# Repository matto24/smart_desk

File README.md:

# Desk Controller

Open-hardware controller for a motorized (sit/stand) desk. A
[Seeed XIAO ESP32-C6](https://wiki.seeedstudio.com/xiao_esp32c6_getting_started/)
measures the desk height with a VL53L1X time-of-flight lidar and drives the
desk's up/down motor lines until it reaches a requested height, exposed over a
small WiFi web server that [Home Assistant](#home-assistant) can control.

> `skrivebord` is Danish for *desk*.

<p align="center">
  
  <br>
  <em>The press-fit 3D-printed enclosure — sensor opening on top, ventilation slots on the front.</em>
</p>

## How it works

- The ESP32-C6 hosts three HTTP endpoints. Each replies only once the action
  is finished, with the measured height as JSON:

  | Request | Action | Reply |
  |---------|--------|-------|
  | `GET /target?cm=90` | Move to 90 cm | `{"height":90.1}` |
  | `GET /nudge?cm=1` (or `-1`) | Move 1 cm up (or down) from where it is | `{"height":91.2}` |
  | `GET /height` | Take one reading | `{"height":92.4}` |

- The lidar is powered off (XSHUT low) except while a request runs.
- On a move it reads the current height, then holds the UP or DOWN line until
  the measured height reaches the target. Within 0.5 cm of the target it does
  not move at all.
- Targets are clamped to a safe range (64–114 cm) and every move has a 20 s
  hard safety timeout, so the motor is never left running.
- A missing or non-numeric `cm` returns `400`; a lidar failure, lost sensor or
  safety timeout returns `503` with `{"error":"..."}`.
- If WiFi drops (e.g. the router restarts), the controller retries every 15 s
  and restarts itself after 5 minutes offline, so it never needs to be
  unplugged to reconnect. At boot it waits at most 30 s for WiFi before
  carrying on and retrying in the background.
- A `/target` or `/nudge` sent while the desk is already moving is answered
  `409` (`{"error":"busy"}`) once the move ends, instead of starting a second
  move. `/nudge` never moves against the requested direction, even if the desk
  is outside 64–114 cm.

## Repository layout

| Path | Contents |
|------|----------|
| `kicad_files/` | KiCad 8 project — schematic, PCB, and fabrication gerbers |
| `casing/` | 3D-printed enclosure — see below |
| `esp_program/` | ESP32-C6 firmware (Arduino / `.ino`) |

### `casing/` — enclosure files

| File | Use |
|------|-----|
| `box_top.3mf` / `box_bottom.3mf` | Ready-to-print halves — press-fit together |
| `box.step` | Neutral CAD for editing in any tool (FreeCAD, SolidWorks, Onshape…) |
| `casing.f3z` | Editable Fusion 360 source archive |

### `esp_program/` — firmware

| File | Use |
|------|-----|
| `main/main.ino` | Main firmware: lidar-guided move-to-height over WiFi |
| `main/desk_logic.h` | Pure height/direction/JSON logic, unit-tested on a computer |
| `tests/run_tests.sh` | Builds and runs those unit tests (`c++`, no hardware needed) |
| `lidar_xshut_test/lidar_xshut_test.ino` | Standalone lidar bring-up / XSHUT test |

## Building the firmware

1. Install the ESP32 board support (Seeed XIAO ESP32-C6) in the Arduino IDE.
2. Install the **VL53L1X** (Pololu) library via Library Manager.
3. Open `esp_program/main/main.ino` and set your WiFi credentials:

   ```cpp
   const char* ssid     = "XXX";   // <- your network
   const char* password = "XXX";   // <- your password
   ```

   > Keep your real credentials out of git — leave the placeholders in the
   > committed copy.

4. Flash to the board, open the serial monitor at 115200 baud to see the
   assigned IP, then move the desk with e.g. `http://<device-ip>/target?cm=90`.

To check the logic without the board, run `esp_program/tests/run_tests.sh`.

## Home Assistant

`homeassistant/packages/desk.yaml` adds the desk to Home Assistant over the
HTTP API above. You don't need MQTT or any add-ons. It gives you:

- **Desk height** (`sensor.desk_height`), updated after every action. The
  lidar is never polled, so the value is the last known height.
- **Desk target** slider (`input_number.desk_target`, 64–114 cm). Moving it
  moves the desk. Restarting Home Assistant does not.
- Scripts **Sit** (72 cm), **Stand** (111 cm), **+1 cm**, **−1 cm** and
  **Measure**. While the desk is moving, further presses are ignored.
- A notification (`Desk`) if the controller replies with an error or can't be
  reached.

Setup:

1. Reserve a fixed IP for the ESP in your router (DHCP reservation).
2. Copy `homeassistant/packages/desk.yaml` to `/config/packages/desk.yaml` on
   Home Assistant (e.g. with the File editor or Samba add-on), and replace
   `DESK_IP` in it with that IP.
3. Make sure `/config/configuration.yaml` loads packages:

   ```yaml
   homeassistant:
     packages: !include_dir_named packages
   ```

4. Check the configuration (Developer tools → YAML → Check configuration) and
   restart Home Assistant.
5. Add a dashboard card (Edit dashboard → Add card → Manual):

   ```yaml
   type: entities
   title: Desk
   entities:
     - sensor.desk_height
     - input_number.desk_target
     - type: buttons
       entities:
         - entity: script.desk_down_1
           name: "-1 cm"
         - entity: script.desk_up_1
           name: "+1 cm"
         - entity: script.desk_sit
           name: Sit
         - entity: script.desk_stand
           name: Stand
         - entity: script.desk_measure
           name: Measure
   ```

To change the presets, edit the `cm:` values in `desk_sit` / `desk_stand`.

## Hardware

- Board / schematic / gerbers: open `kicad_files/skrivebord.kicad_pro` in
  KiCad 10. `kicad_files/gerbers/desktop_control_v1.zip` is the packaged
  fabrication output.
- Enclosure: print `box_top.3mf` and `box_bottom.3mf` and press-fit.

## License

Released under the [MIT License](LICENSE) — free to use, modify, and
distribute, keep the copyright notice. The bundled Seeed XIAO KiCad libraries
under `kicad_files/libraries/` remain the property of Seeed Studio.

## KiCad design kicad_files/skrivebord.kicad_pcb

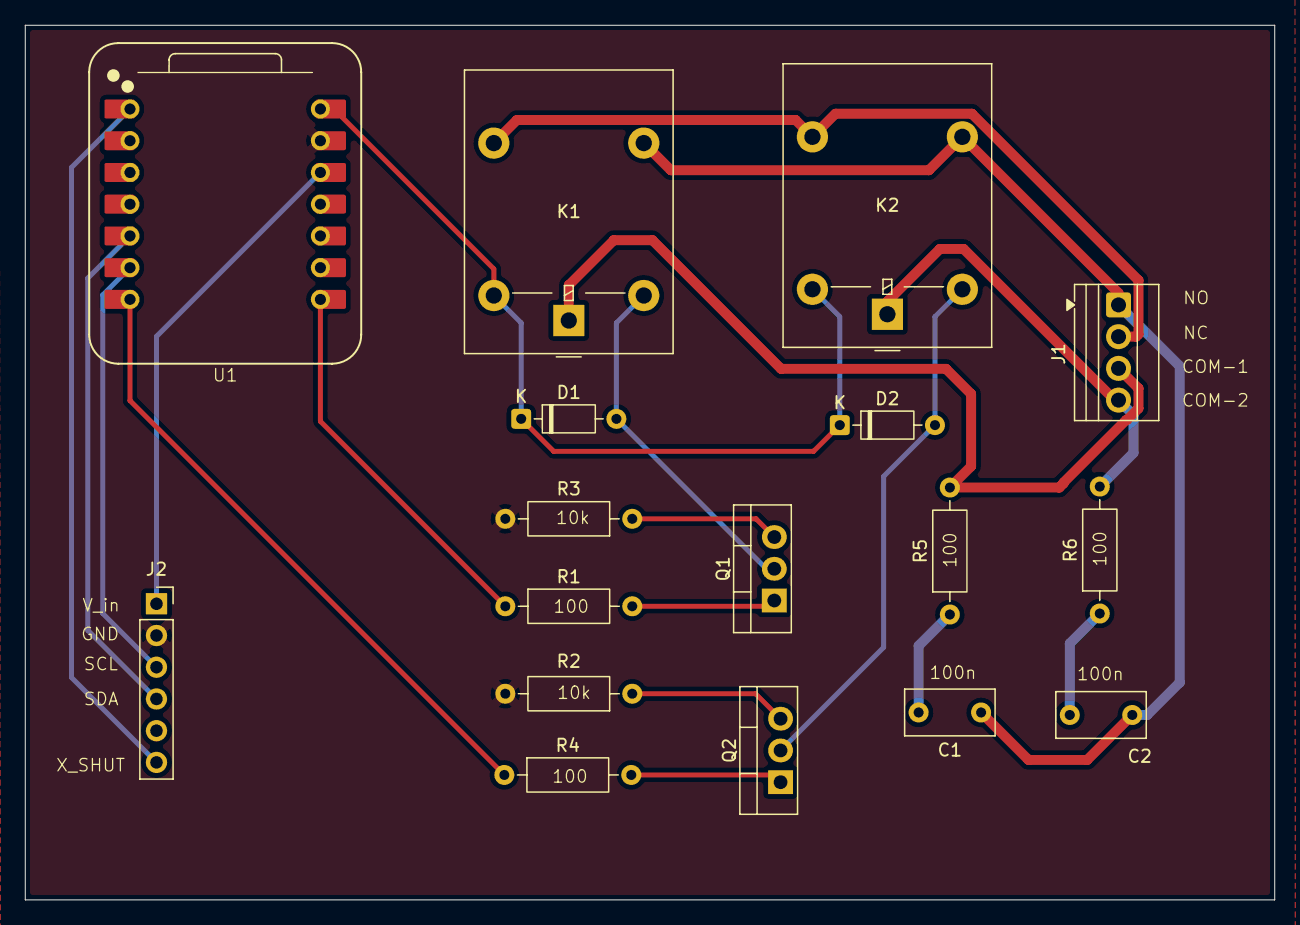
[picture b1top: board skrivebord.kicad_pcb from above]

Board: 2 copper layers, 100.0 x 70.0 mm, 17 parts (0 on the bottom side), 20 nets.

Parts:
C1, C2: 100n; C_Rect_L7.0mm_W3.5mm_P5.00mm
D1, D2: 1N914; D_DO-35_SOD27_P7.62mm_Horizontal
J1: Screw_Terminal_01x04; TerminalBlock_Xinya_XY308-2.54-4P_1x04_P2.54mm_Horizontal
J2: Conn_01x06; PinSocket_1x06_P2.54mm_Vertical
K1, K2: G5LE-1; Relay_SPDT_Omron-G5LE-1
Q1, Q2: IRLZ34N; TO-220-3_Vertical
R1, R4, R5, R6: 100; R_Axial_DIN0207_L6.3mm_D2.5mm_P10.16mm_Horizontal
R2, R3: 10K; R_Axial_DIN0207_L6.3mm_D2.5mm_P10.16mm_Horizontal
U1: XIAO-ESP32-C6-DIP

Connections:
+3.3V: J2.1, U1.12 (3V3)
+5V: D1.1 (K), D2.1 (K), K1.5, K2.5, U1.14 (VBUS)
GND: J2.2, R2.2, R3.2, U1.13 (GND)
unnamed: C1.2, R5.1
unnamed: C2.2, R6.1
unnamed: D1.2 (A), K1.2, Q1.2 (D)
unnamed: D2.2 (A), K2.2, Q2.2 (D)
unnamed: J1.3 (COM_1), K1.1, R5.2
unnamed: J1.4 (COM_2), K2.1, R6.2
unnamed: J1.2 (NC), K1.4, K2.4
unnamed: C1.1, C2.1, J1.1 (NO), K1.3, K2.3
unnamed: J2.3, U1.6 (GPIO23_D5_SCL)
unnamed: J2.4, U1.5 (GPIO22_D4_SDA)
unnamed: J2.6, U1.1 (GPIO0_A0_D0)
unnamed: Q1.1 (G), R1.2
unnamed: Q1.3 (S), R3.1
unnamed: Q2.1 (G), R4.2
unnamed: Q2.3 (S), R2.1
unnamed: R4.1, U1.7 (GPIO16_D6_TX)
unnamed: R1.1, U1.8 (GPIO17_D7_RX)
